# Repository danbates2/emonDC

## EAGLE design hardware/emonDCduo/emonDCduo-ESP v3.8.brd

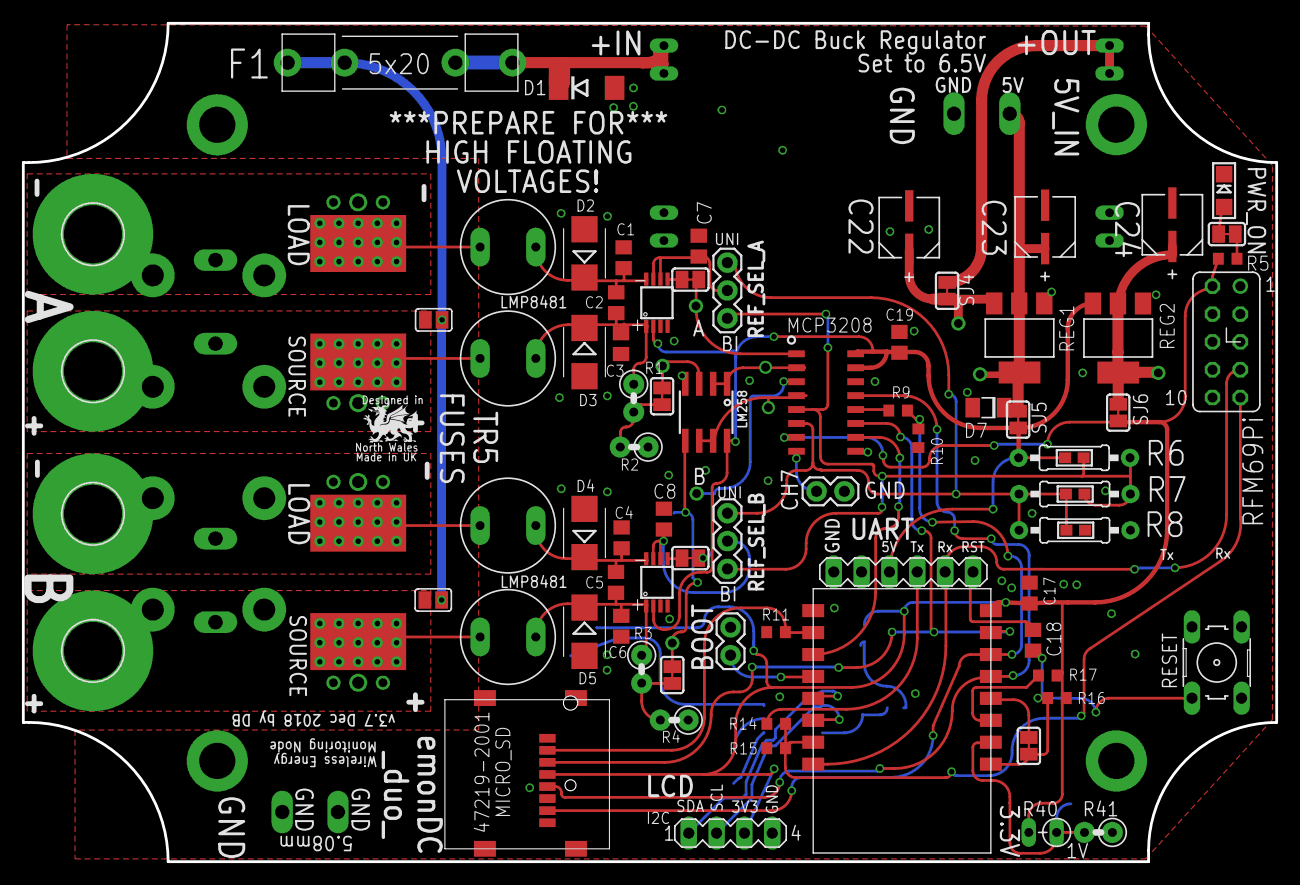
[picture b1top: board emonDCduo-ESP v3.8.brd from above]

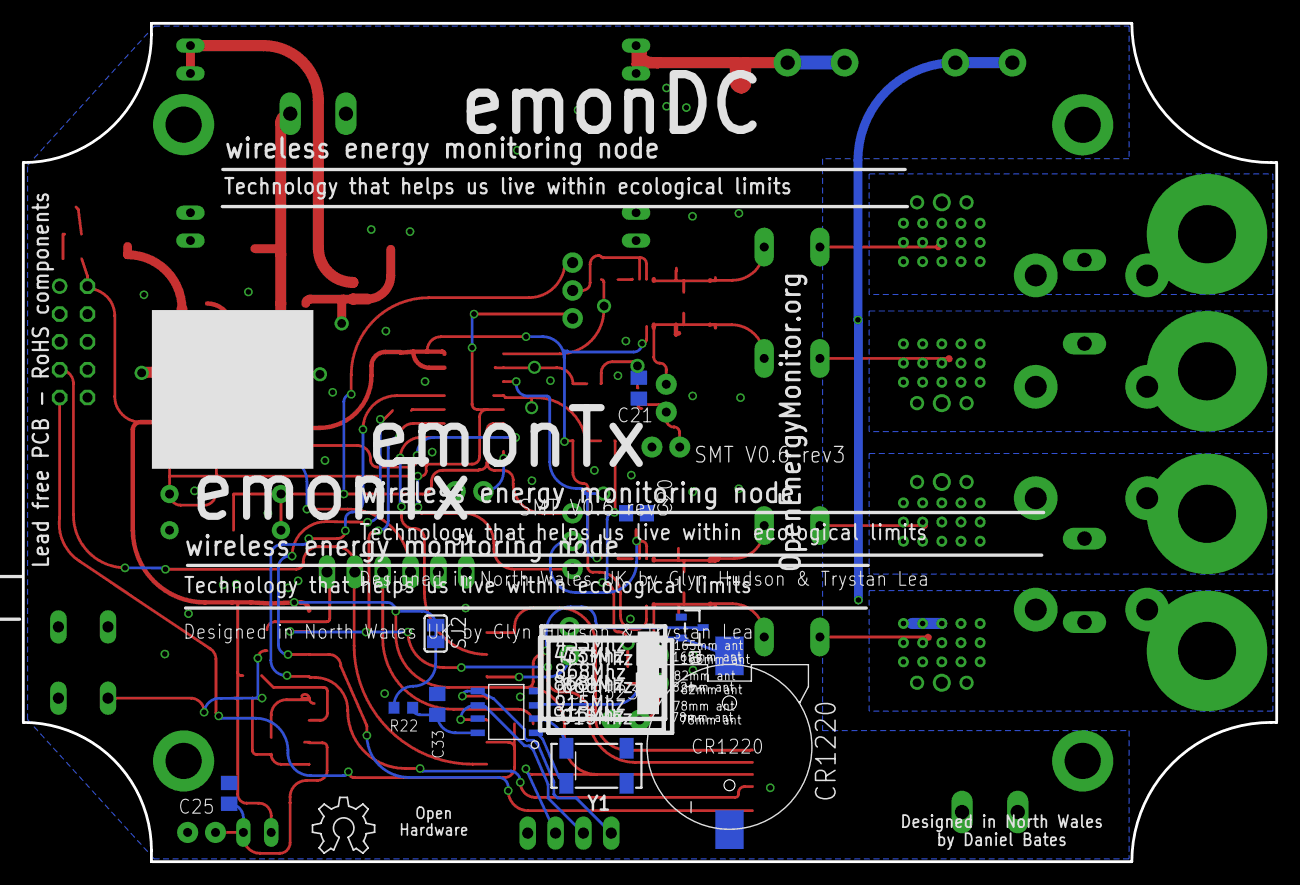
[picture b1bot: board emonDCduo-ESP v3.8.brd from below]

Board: 2 copper layers, 114.3 x 76.5 mm, 109 parts (12 on the bottom side), 56 nets.

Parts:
BOOT: 1X02
C1, C3, C4, C6, C7, C8: 0.1uF 100V; C0805
C2, C5, C20, C21: 1nF 100V; C0805
C17, C18, C19, C25: 0.1uF; C0805
C22, C23, C24: 100UF; CAPAE530X610N
C33: 4.7uF; C0805
CR1220: CR1220SMD
D1: P6SMB75A; DO214AA
D2, D3, D4, D5: P6SMB75A; SMB
D7: SMF6.0A; SOD123F
EBW_A: EBW_SERIES_15.2MM
EBW_B: EBW_SERIES_15.2MM
ESP-12: ESP8266_ESP-12; ESP8266-ESP12
F1: 445/030_SERIES; 445/030_SERIES_LITTELFUSE
F2, F3, F4, F5: TR5
GPIO_1: FE05-2_RFM69PI_OULTINE
J5: 1X02
LED1: PWR_ON; CHIPLED_1206
LM258: SOIC8_150MIL
LOGO1: OSHW_LOGO_6MILX0200-NT; OSHW_6X200_NOTEXT
MCP3208: MCP3208-BI/SL; SOIC16
MH1, MH2, MH3, MH4: 5.3mm; 5,3//11-PAD
MICRO_SD: 47219-2001_MICROSD
MOUNT_10.16_A, MOUNT_10.16_B: MOLEX_39970-003; 2/10,16
PCF8523: PCF8523_RTC; SOIC_8
Q1: SOT23-R
R1, R3: 1M 100V; 0207/2V
R2, R4: 56K; 0207/2V
R5: 174R; R0603
R6: 10k; 0207/10
R7: 3.3k; 0207/10
R8: 180R; 0207/10
R9, R22: 1K; R0603
R10: 2K; R0603
R11, R16, R17: 10K; R0603
R14: 1k; R0603
R15: 2k; R0603
R25: 10k; 0603
R26: 3.3k; 0603
R27: 180R; 0603
R40: THERMISTOR-2,5; RS-2,5
R41: 0207/2V
REF_SEL_A: 455-1750-1-ND; 1X03
REF_SEL_B: 455-1750-1-ND; 1X03
REG1: REG1117-5.0V; SOT223
REG2: REG1117-3.3V; SOT223
RESET: RESET_BUTT; B3F-10XX
SHUNTMON-A: LMP8481; S-PDSO-G08
SHUNTMON-B: LMP8481; S-PDSO-G08
SJ2, SJ4, SJ5, SJ6, SJ8, SJ9, SJ10, SJ11, SJ12, SJ13: SOLDERJUMPER_CLOSEDWIRE
SJ3, SJ7: SJ
SV1: MA04-1
TP8, TP9, TP10, TP11: TPPAD1-13Y; P1-13Y
U$1, U$4, U$5, U$6, U$7, U$8, U$9: TP0.8MM; TP0.8
U$2, U$3, U$10, U$11: 2212S-02SG-85; TP0.8_X2
U$12, U$13: 5MMBLOCK; 2/5.08
UART: UART; MA06-1
Y1: 32Khz; CRYSTAL_8X3.8

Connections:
3.3V_PRE: C24.1, REG2.2, REG2.4, SJ6.1, U$8.P$1
5V_PRE: C23.1, D7.C, REG1.2, REG1.4, SJ5.1, U$7.P$1, U$12.P$1
6.5V: C22.1, REG1.3, SJ4.2, U$9.P$1
+3V3: C17.2, ESP-12.16, GPIO_1.2, MCP3208.7, MICRO_SD.PIN4, Q1.3, R5.2, R16.2, R17.2, R40.2, SJ2.1, SJ6.2, SV1.3
+5V: C19.1, LM258.8, MCP3208.15, MCP3208.16, R6.2, R25.2, REG2.3, SHUNTMON-A.2, SHUNTMON-B.2, SJ5.2, UART.4
ADC: C25.1, ESP-12.10, R40.1, R41.2
ADCSHUNT_A: MCP3208.1, SJ11.2, U$6.P$1
ADCSHUNT_B: MCP3208.3, SJ10.2, U$5.P$1
BI_REF: MCP3208.5, R6.1, R7.2, R25.1, R26.2, REF_SEL_A.3, REF_SEL_B.3
CH7: J5.1, MCP3208.8
CH_PD: ESP-12.11, R17.1
D0/RX: ESP-12.8, GPIO_1.7, UART.2
D1/TX: ESP-12.7, GPIO_1.9, R14.2, R15.1
GND: BOOT.1, C1.2, C3.2, C4.2, C6.2, C7.2, C8.2, C17.1, C19.2, C20.2, C21.2, C22.2, C23.2, C24.2, C25.2, C33.2, CR1220.P-, D1.A, D2.A, D3.A, D4.A, D5.A, D7.A, ESP-12.1, GPIO_1.5, GPIO_1.10, J5.2, LED1.C, LM258.4, MCP3208.9, MCP3208.14, MICRO_SD.P$1, MICRO_SD.P$2, MICRO_SD.P$3, MICRO_SD.P$4, MICRO_SD.PIN6, PCF8523.4, Q1.1, R2.1, R4.1, R8.1, R10.2, R11.2, R15.2, R27.1, R41.1, REG1.1, REG2.1, RESET.3, SHUNTMON-A.4, SHUNTMON-B.4, SV1.4, U$3.P$1, U$3.P$2, U$11.P$1, U$11.P$2, U$12.P$3, U$13.P$1, U$13.P$3, UART.6
GPIO0: BOOT.2, ESP-12.4
GPIO2: ESP-12.3, MCP3208.10
GPIO12: ESP-12.14, MICRO_SD.PIN7, R9.2, R10.1
GPIO12A: MCP3208.12, R9.1
GPIO13: ESP-12.15, MCP3208.11, MICRO_SD.PIN3
GPIO14: ESP-12.13, MCP3208.13, MICRO_SD.PIN5
GPIO15: ESP-12.2, MICRO_SD.PIN2, R11.1
GPIO16: ESP-12.12, SJ12.1
LOAD-NEG-A: EBW_B.P$2, EBW_B.P$18, EBW_B.P$19, EBW_B.P$20, EBW_B.P$21, EBW_B.P$22, EBW_B.P$23, EBW_B.P$24, EBW_B.P$25, EBW_B.P$26, EBW_B.P$27, EBW_B.P$28, EBW_B.P$29, EBW_B.P$30, EBW_B.P$31, EBW_B.P$32, EBW_B.P$36, EBW_B.P$37, EBW_B.P$38, F2.1, MH2.B5,5, MOUNT_10.16_A.P$1, MOUNT_10.16_A.P$2, TP11.TP
LOAD-NEG-A_T: C1.1, C2.1, D2.C, F2.2, SHUNTMON-A.8
LOAD-NEG-B: EBW_A.P$2, EBW_A.P$18, EBW_A.P$19, EBW_A.P$20, EBW_A.P$21, EBW_A.P$22, EBW_A.P$23, EBW_A.P$24, EBW_A.P$25, EBW_A.P$26, EBW_A.P$27, EBW_A.P$28, EBW_A.P$29, EBW_A.P$30, EBW_A.P$31, EBW_A.P$32, EBW_A.P$36, EBW_A.P$37, EBW_A.P$38, F4.1, MH4.B5,5, MOUNT_10.16_B.P$1, MOUNT_10.16_B.P$2, TP9.TP
LOAD-NEG-B_T: C4.1, C5.1, D4.C, F4.2, SHUNTMON-B.8
unnamed: C18.1, UART.1
unnamed: R5.1, SJ13.1
unnamed: LED1.A, SJ13.2
unnamed: SHUNTMON-B.5, SJ10.1
unnamed: SHUNTMON-A.5, SJ11.1
unnamed: R14.1, UART.3
unnamed: PCF8523.2, Y1.P$4
unnamed: PCF8523.1, Y1.P$1
REF_A_INPUT: C7.1, REF_SEL_A.2, SHUNTMON-A.6, SHUNTMON-A.7
REF_B_INPUT: C8.1, REF_SEL_B.2, SHUNTMON-B.6, SHUNTMON-B.7
RST: C18.2, ESP-12.9, R16.1, RESET.1, SJ12.2
SCL: ESP-12.6, PCF8523.6, SV1.2
SDA: ESP-12.5, PCF8523.5, SV1.1
SOURCE-POS-A: EBW_B.P$1, EBW_B.P$3, EBW_B.P$4, EBW_B.P$5, EBW_B.P$6, EBW_B.P$7, EBW_B.P$8, EBW_B.P$9, EBW_B.P$10, EBW_B.P$11, EBW_B.P$12, EBW_B.P$13, EBW_B.P$14, EBW_B.P$15, EBW_B.P$16, EBW_B.P$17, EBW_B.P$33, EBW_B.P$34, EBW_B.P$35, F3.1, MH1.B5,5, MOUNT_10.16_A.P$3, MOUNT_10.16_A.P$4, SJ3.2, TP10.TP
SOURCE-POS-A_T: C2.2, C3.1, D3.C, F3.2, R1.1, SHUNTMON-A.1
SOURCE-POS-B: EBW_A.P$1, EBW_A.P$3, EBW_A.P$4, EBW_A.P$5, EBW_A.P$6, EBW_A.P$7, EBW_A.P$8, EBW_A.P$9, EBW_A.P$10, EBW_A.P$11, EBW_A.P$12, EBW_A.P$13, EBW_A.P$14, EBW_A.P$15, EBW_A.P$16, EBW_A.P$17, EBW_A.P$33, EBW_A.P$34, EBW_A.P$35, F5.1, MH3.B5,5, MOUNT_10.16_B.P$3, MOUNT_10.16_B.P$4, SJ7.1, TP8.TP
SOURCE-POS-B_T: C5.2, C6.1, D5.C, F5.2, R3.1, SHUNTMON-B.1
UNI_REF: MCP3208.6, R7.1, R8.2, R26.1, R27.2, REF_SEL_A.1, REF_SEL_B.1
VBAT: CR1220.P+, PCF8523.3, Q1.2
VDD_PCF: C33.1, PCF8523.8, R22.1
VDD_RTC_POSTJUMPER: R22.2, SJ2.2
VOUT_POST_SWITCHING: SJ4.1, U$10.P$1, U$10.P$2
VSENSE_A: R1.2, R2.2, SJ8.1
VSENSE_A_BUFFED: LM258.1, LM258.2, MCP3208.2
VSENSE_A_TP: C21.1, LM258.3, SJ8.2, U$1.P$1
VSENSE_B: R3.2, R4.2, SJ9.1
VSENSE_B_BUFFED: LM258.6, LM258.7, MCP3208.4
VSENSE_B_TP: C20.1, LM258.5, SJ9.2, U$4.P$1
V_IN_POSTFUSE: D1.C, F1.P$3, F1.P$4, U$2.P$1, U$2.P$2
V_IN_PREFUSE: F1.P$1, F1.P$2, SJ3.1, SJ7.2

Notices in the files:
parts and their libraries:
SparkFun-Connectors: Licensing: CC v3.0 Share-Alike You are welcome to use this library for commercial purposes.
microbuilder: This work is placed in the public domain, and may be freely used for commercial and non-commercial work with the following conditions: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
